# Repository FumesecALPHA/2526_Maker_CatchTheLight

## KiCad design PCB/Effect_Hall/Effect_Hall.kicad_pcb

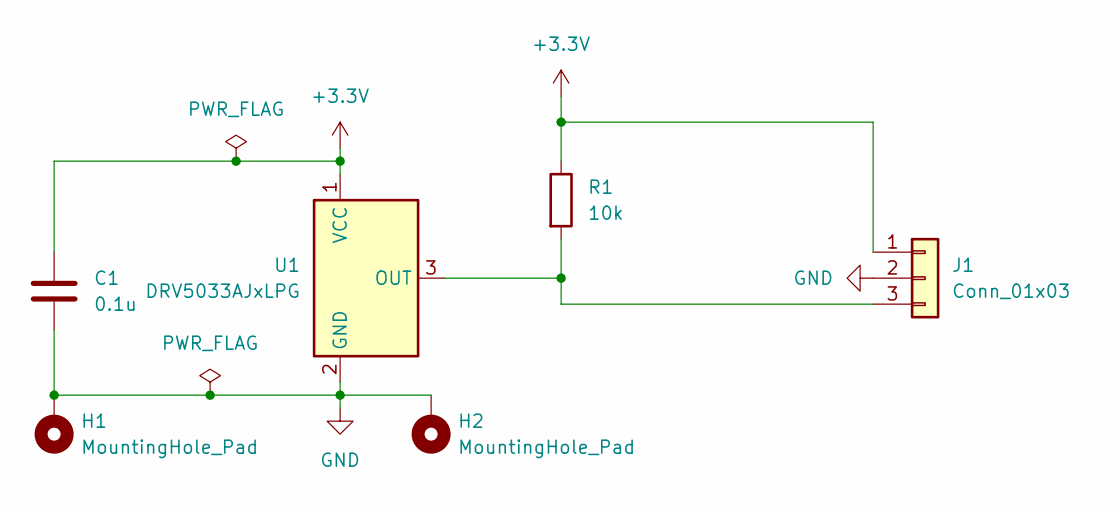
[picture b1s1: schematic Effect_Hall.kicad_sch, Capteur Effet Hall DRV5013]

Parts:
C1: 0.1u; C_0805_2012Metric_Pad1.18x1.45mm_HandSolder
H1, H2: MountingHole_Pad; MountingHole_2.7mm_M2.5_DIN965_Pad
J1: Conn_01x03; JST_EH_B3B-EH-A_1x03_P2.50mm_Vertical
R1: 10k; R_0805_2012Metric_Pad1.20x1.40mm_HandSolder
U1: DRV5033AJxLPG; TO-92Flat

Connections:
+3.3V: C1.1, J1.1, R1.1, U1.1 (VCC)
GND: C1.2, H1.1, H2.1, J1.2, U1.2 (GND)
unnamed: J1.3, R1.2, U1.3 (OUT)

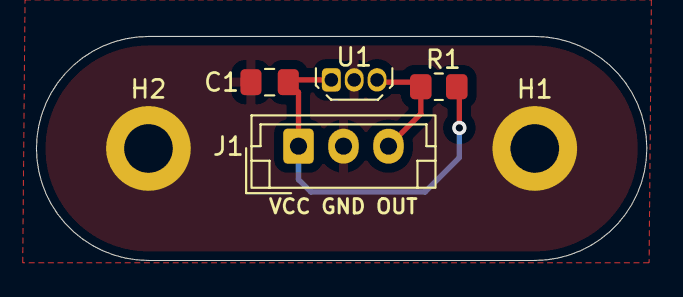
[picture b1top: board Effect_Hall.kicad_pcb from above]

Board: 2 copper layers, 33.9 x 12.4 mm, 6 parts (0 on the bottom side), 3 nets.

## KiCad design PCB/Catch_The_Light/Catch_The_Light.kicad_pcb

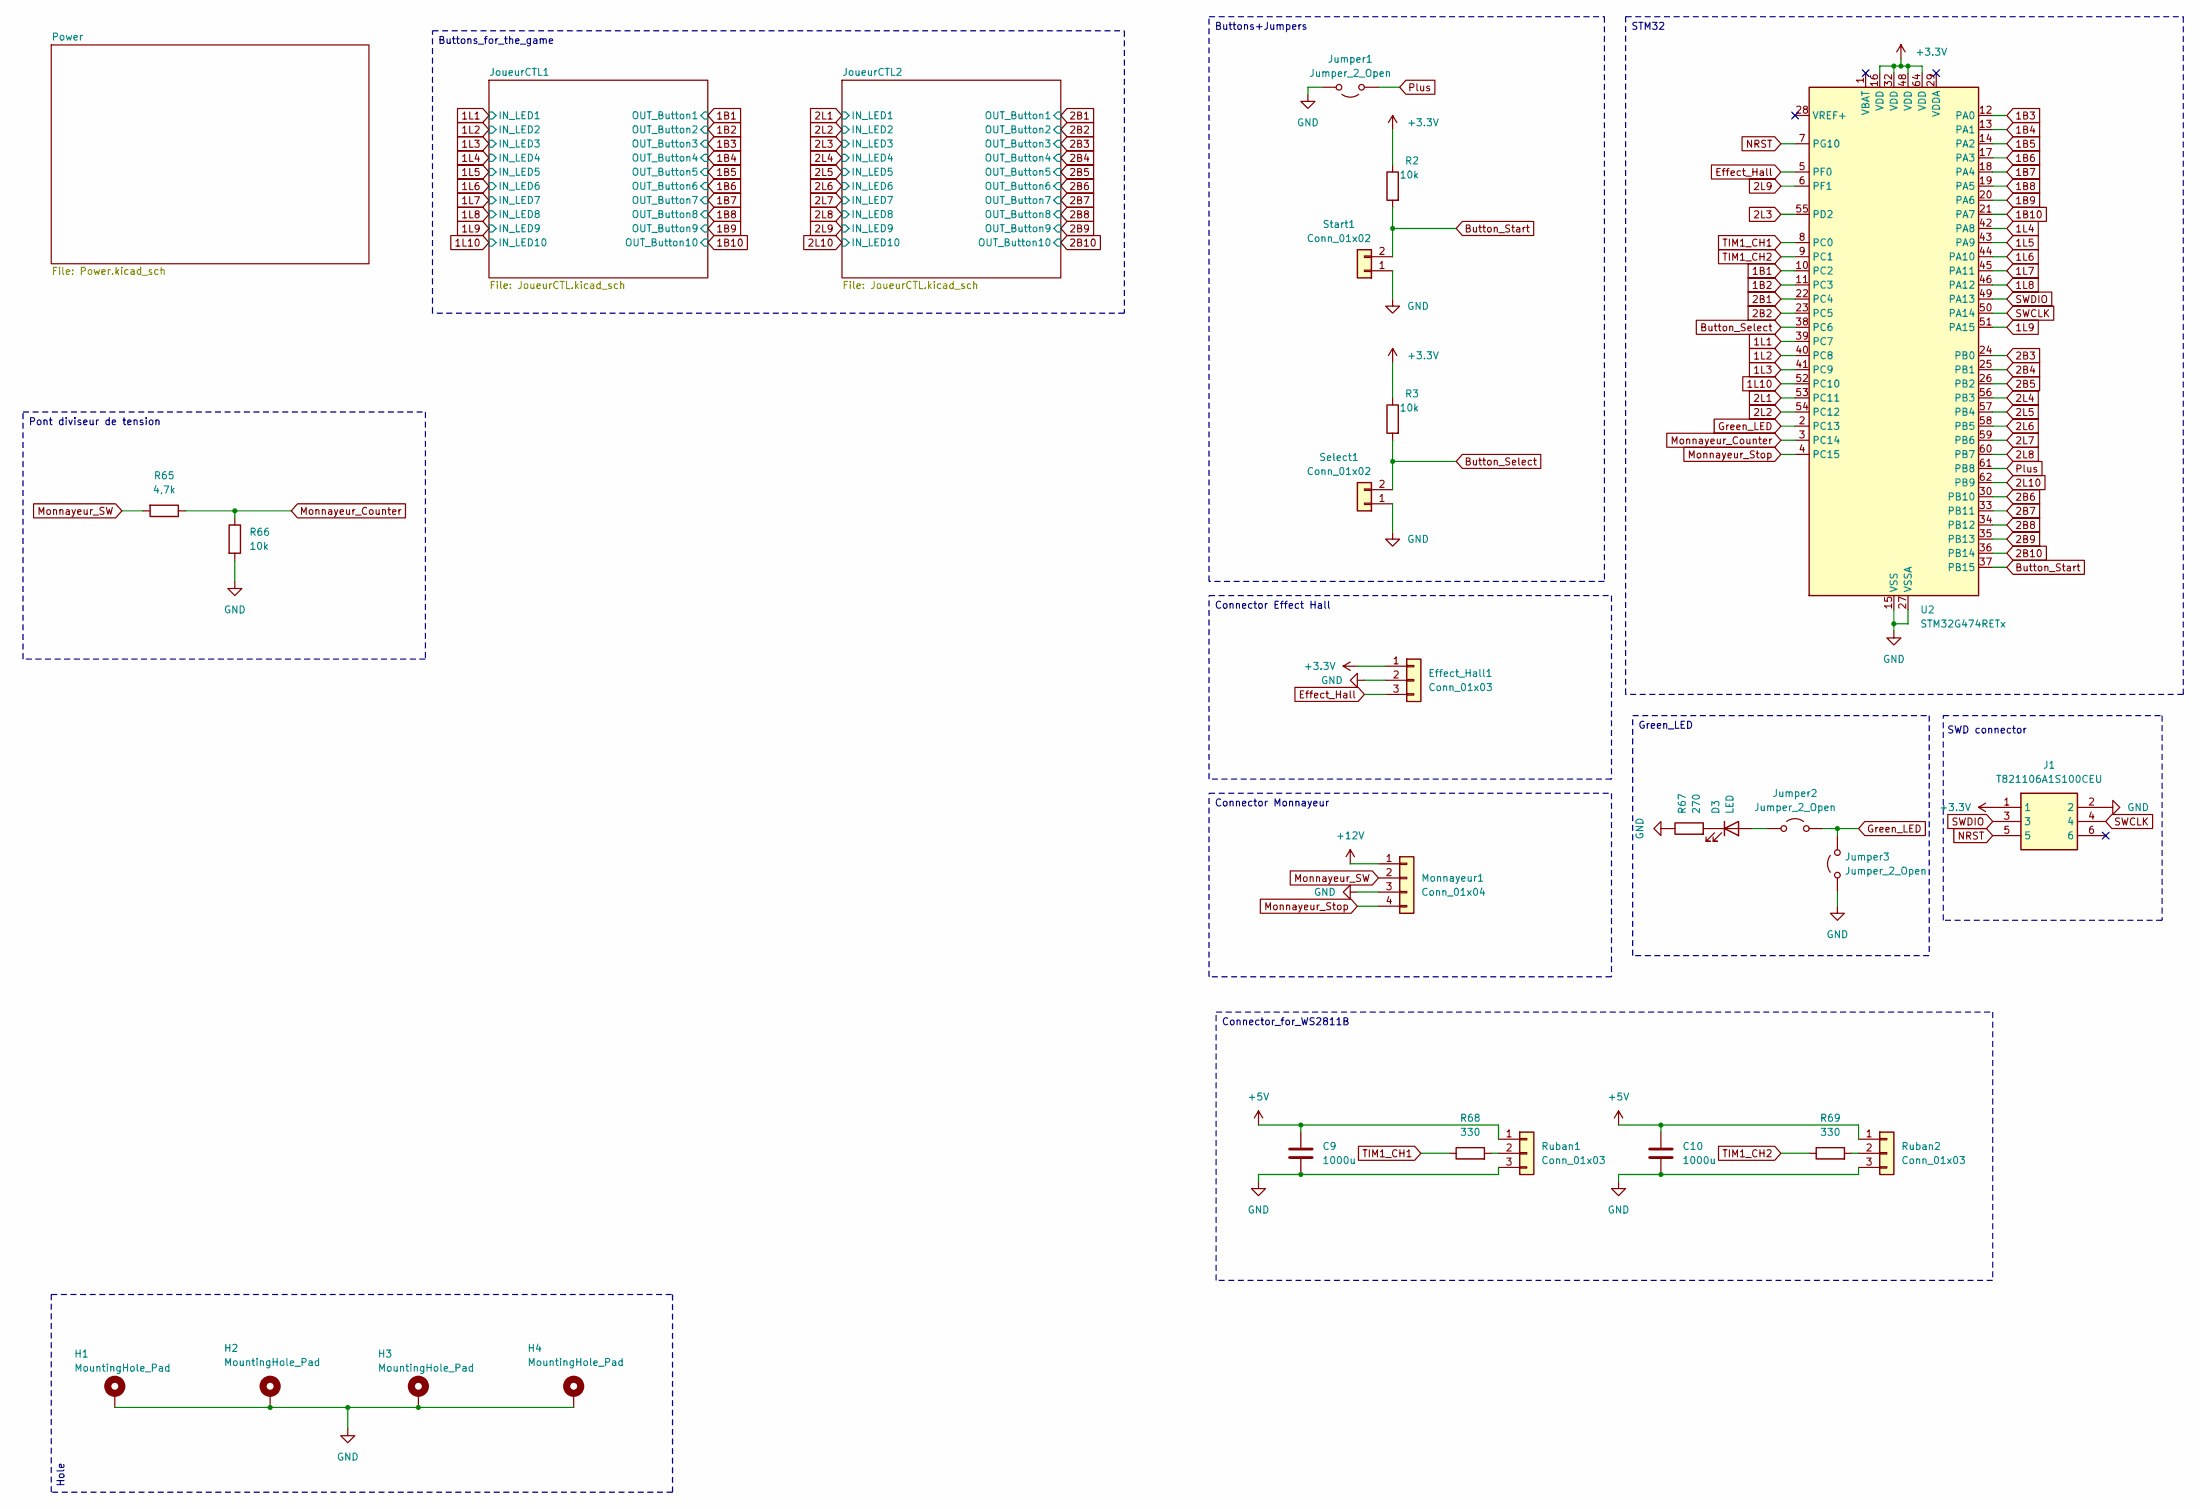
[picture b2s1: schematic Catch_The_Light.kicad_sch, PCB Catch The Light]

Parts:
C9, C10: 1000u; C_0402_1005Metric_Pad0.74x0.62mm_HandSolder
D3: LED; LED_0805_2012Metric_Pad1.15x1.40mm_HandSolder
Effect_Hall1: Conn_01x03; JST_EH_B3B-EH-A_1x03_P2.50mm_Vertical
H1, H2, H3, H4: MountingHole_Pad; MountingHole_3.2mm_M3_DIN965_Pad
J1: T821106A1S100CEU; PinHeader_2x03_P2.54mm_Vertical_SMD; Manufacturer_Part_Number T821106A1S100CEU
Jumper1, Jumper2, Jumper3: Jumper_2_Open; PinHeader_1x02_P2.54mm_Vertical
Monnayeur1: Conn_01x04; JST_EH_B4B-EH-A_1x04_P2.50mm_Vertical
R2, R3, R66: 10k; R_0402_1005Metric_Pad0.72x0.64mm_HandSolder
R65: 4,7k; R_0402_1005Metric_Pad0.72x0.64mm_HandSolder
R67: 270; R_0402_1005Metric_Pad0.72x0.64mm_HandSolder
R68, R69: 330; R_0402_1005Metric_Pad0.72x0.64mm_HandSolder
Ruban1, Ruban2: Conn_01x03; JST_EH_B3B-EH-A_1x03_P2.50mm_Vertical
Select1: Conn_01x02; JST_EH_B2B-EH-A_1x02_P2.50mm_Vertical
Start1: Conn_01x02; JST_EH_B2B-EH-A_1x02_P2.50mm_Vertical
U2: STM32G474RETx; LQFP-64_10x10mm_P0.5mm

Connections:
1B1: U2.10 (PC2); also elsewhere on the board
1B2: U2.11 (PC3); also elsewhere on the board
1B3: U2.12 (PA0); also elsewhere on the board
1B4: U2.13 (PA1); also elsewhere on the board
1B5: U2.14 (PA2); also elsewhere on the board
1B6: U2.17 (PA3); also elsewhere on the board
1B7: U2.18 (PA4); also elsewhere on the board
1B8: U2.19 (PA5); also elsewhere on the board
1B9: U2.20 (PA6); also elsewhere on the board
1B10: U2.21 (PA7); also elsewhere on the board
1L1: U2.39 (PC7); also elsewhere on the board
1L2: U2.40 (PC8); also elsewhere on the board
1L3: U2.41 (PC9); also elsewhere on the board
1L4: U2.42 (PA8); also elsewhere on the board
1L5: U2.43 (PA9); also elsewhere on the board
1L6: U2.44 (PA10); also elsewhere on the board
1L7: U2.45 (PA11); also elsewhere on the board
1L8: U2.46 (PA12); also elsewhere on the board
1L9: U2.51 (PA15); also elsewhere on the board
1L10: U2.52 (PC10); also elsewhere on the board
2B1: U2.22 (PC4); also elsewhere on the board
2B2: U2.23 (PC5); also elsewhere on the board
2B3: U2.24 (PB0); also elsewhere on the board
2B4: U2.25 (PB1); also elsewhere on the board
2B5: U2.26 (PB2); also elsewhere on the board
2B6: U2.30 (PB10); also elsewhere on the board
2B7: U2.33 (PB11); also elsewhere on the board
2B8: U2.34 (PB12); also elsewhere on the board
2B9: U2.35 (PB13); also elsewhere on the board
2B10: U2.36 (PB14); also elsewhere on the board
2L1: U2.53 (PC11); also elsewhere on the board
2L2: U2.54 (PC12); also elsewhere on the board
2L3: U2.55 (PD2); also elsewhere on the board
2L4: U2.56 (PB3); also elsewhere on the board
2L5: U2.57 (PB4); also elsewhere on the board
2L6: U2.58 (PB5); also elsewhere on the board
2L7: U2.59 (PB6); also elsewhere on the board
2L8: U2.60 (PB7); also elsewhere on the board
2L9: U2.6 (PF1); also elsewhere on the board
2L10: U2.62 (PB9); also elsewhere on the board
+3.3V: Effect_Hall1.1, J1.1, R2.1, R3.1, U2.16 (VDD), U2.32 (VDD), U2.48 (VDD), U2.64 (VDD); also elsewhere on the board
+5V: C9.1, C10.1, Ruban1.1, Ruban2.1; also elsewhere on the board
+12V: Monnayeur1.1; also elsewhere on the board
Button_Select: R3.2, Select1.2, U2.38 (PC6)
Button_Start: R2.2, Start1.2, U2.37 (PB15)
Effect_Hall: Effect_Hall1.3, U2.5 (PF0)
GND: C9.2, C10.2, Effect_Hall1.2, H1.1, H2.1, H3.1, H4.1, J1.2, Jumper1.1 (A), Jumper3.2 (B), Monnayeur1.3, R66.2, R67.1, Ruban1.3, Ruban2.3, Select1.1, Start1.1, U2.15 (VSS), U2.27 (VSSA), U2.31 (VSS), U2.47 (VSS), U2.63 (VSS); also elsewhere on the board
Green_LED: Jumper2.1 (A), Jumper3.1 (A), U2.2 (PC13)
Monnayeur_Counter: R65.1, R66.1, U2.3 (PC14)
Monnayeur_SW: Monnayeur1.2, R65.2
Monnayeur_Stop: Monnayeur1.4, U2.4 (PC15)
NRST: J1.5, U2.7 (PG10)
unnamed: D3.2 (A), Jumper2.2 (B)
unnamed: D3.1 (K), R67.2
unnamed: R68.2, Ruban1.2
unnamed: R69.2, Ruban2.2
Plus: Jumper1.2 (B), U2.61 (PB8)
SWCLK: J1.4, U2.50 (PA14)
SWDIO: J1.3, U2.49 (PA13)
TIM1_CH1: R68.1, U2.8 (PC0)
TIM1_CH2: R69.1, U2.9 (PC1)

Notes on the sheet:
SWD connector
Green_LED
Connector Monnayeur
Hole
Buttons_for_the_game
Connector_for_WS2811B
STM32
Pont diviseur de tension
Buttons+Jumpers
Connector Effect Hall

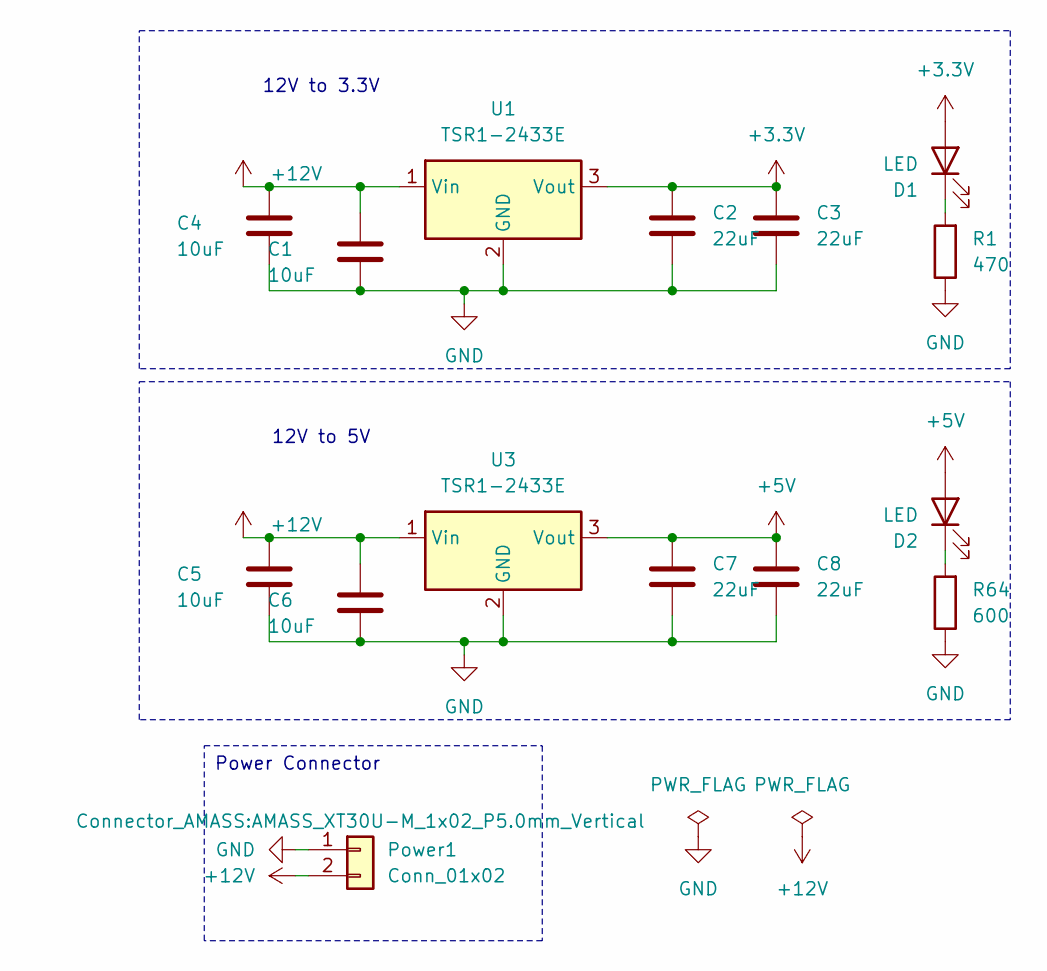
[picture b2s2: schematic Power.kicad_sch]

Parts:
C1, C4, C5, C6: 10uF; C_0402_1005Metric_Pad0.74x0.62mm_HandSolder
C2, C3, C7, C8: 22uF; C_0402_1005Metric_Pad0.74x0.62mm_HandSolder
D1, D2: LED; LED_0805_2012Metric_Pad1.15x1.40mm_HandSolder
Power1: Conn_01x02; AMASS_XT30U-M_1x02_P5.0mm_Vertical
R1: 470; R_0402_1005Metric_Pad0.72x0.64mm_HandSolder
R64: 600; R_0402_1005Metric_Pad0.72x0.64mm_HandSolder
U1, U3: TSR1-2433E; 173010335

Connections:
+3.3V: C2.2, C3.2, D1.2 (A), U1.3 (Vout); also elsewhere on the board
+5V: C7.2, C8.2, D2.2 (A), U3.3 (Vout); also elsewhere on the board
+12V: C1.2, C4.2, C5.2, C6.2, Power1.2, U1.1 (Vin), U3.1 (Vin); also elsewhere on the board
GND: C1.1, C2.1, C3.1, C4.1, C5.1, C6.1, C7.1, C8.1, Power1.1, R1.1, R64.1, U1.2 (GND), U3.2 (GND); also elsewhere on the board
unnamed: D1.1 (K), R1.2
unnamed: D2.1 (K), R64.2

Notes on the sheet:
12V to 5V
12V to 3.3V
Power Connector

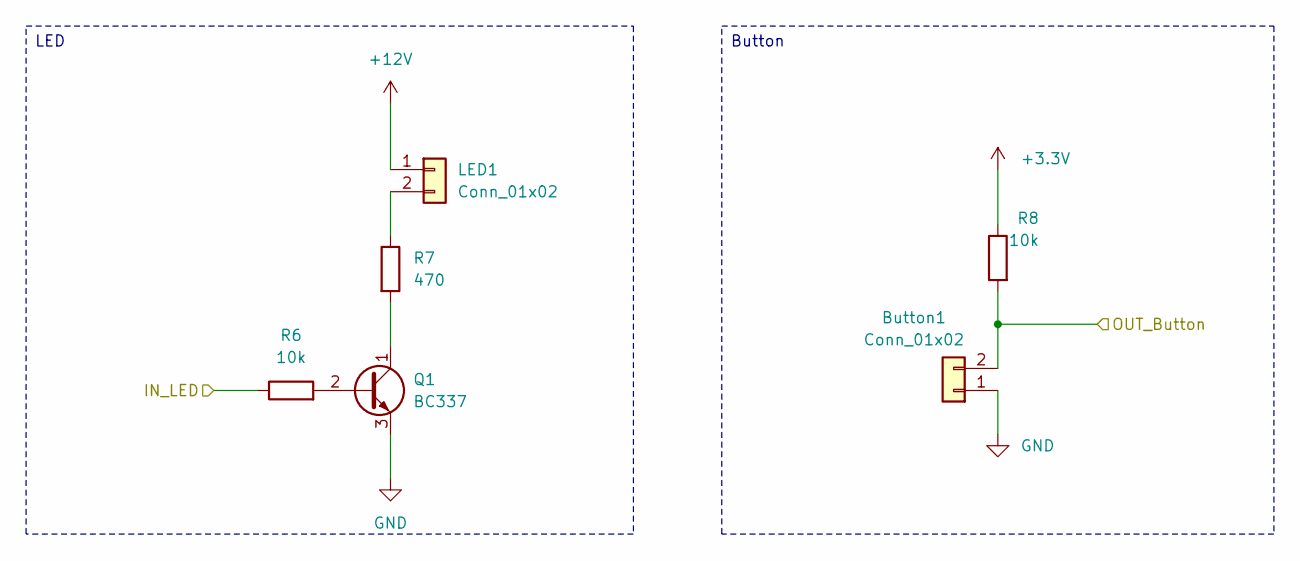
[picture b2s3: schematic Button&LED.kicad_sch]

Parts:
Button1: Conn_01x02; JST_EH_B2B-EH-A_1x02_P2.50mm_Vertical
LED1: Conn_01x02; JST_EH_B2B-EH-A_1x02_P2.50mm_Vertical
Q1: BC337; TO-92_Inline
R6, R8: 10k; R_0402_1005Metric_Pad0.72x0.64mm_HandSolder
R7: 470; R_0402_1005Metric_Pad0.72x0.64mm_HandSolder

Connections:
1B1: Button1.2, R8.2; also elsewhere on the board
1L1: R6.1; also elsewhere on the board
+3.3V: R8.1; also elsewhere on the board
+12V: LED1.1; also elsewhere on the board
GND: Button1.1, Q1.3 (E); also elsewhere on the board
unnamed: LED1.2, R7.1
unnamed: Q1.2 (B), R6.2
unnamed: Q1.1 (C), R7.2

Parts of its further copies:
Button2, Button3, Button4, Button5, Button6, Button7, Button8, Button9, Button10, Button11, Button12, Button13, Button14, Button15, Button16, Button17, Button18, Button19, Button20: Conn_01x02; JST_EH_B2B-EH-A_1x02_P2.50mm_Vertical
LED2, LED3, LED4, LED5, LED6, LED7, LED8, LED9, LED10, LED11, LED12, LED13, LED14, LED15, LED16, LED17, LED18, LED19, LED20: Conn_01x02; JST_EH_B2B-EH-A_1x02_P2.50mm_Vertical
Q2, Q3, Q4, Q5, Q6, Q7, Q8, Q9, Q10, Q11, Q12, Q13, Q14, Q15, Q16, Q17, Q18, Q19, Q20: BC337; TO-92_Inline
R4, R9, R11, R12, R14, R15, R17, R18, R20, R21, R23, R24, R26, R27, R29, R30, R32, R33, R35, R36, R37, R39, R40, R42, R43, R45, R46, R48, R49, R51, R52, R54, R55, R57, R58, R60, R61, R63: 10k; R_0402_1005Metric_Pad0.72x0.64mm_HandSolder
R5, R10, R13, R16, R19, R22, R25, R28, R31, R34, R38, R41, R44, R47, R50, R53, R56, R59, R62: 470; R_0402_1005Metric_Pad0.72x0.64mm_HandSolder

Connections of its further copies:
1B2: Button2.2, R11.2; also elsewhere on the board
1B3: Button3.2, R14.2; also elsewhere on the board
1B4: Button4.2, R17.2; also elsewhere on the board
1B5: Button5.2, R20.2; also elsewhere on the board
1B6: Button6.2, R23.2; also elsewhere on the board
1B7: Button7.2, R26.2; also elsewhere on the board
1B8: Button8.2, R29.2; also elsewhere on the board
1B9: Button9.2, R32.2; also elsewhere on the board
1B10: Button10.2, R35.2; also elsewhere on the board
1L2: R9.1; also elsewhere on the board
1L3: R12.1; also elsewhere on the board
1L4: R15.1; also elsewhere on the board
1L5: R18.1; also elsewhere on the board
1L6: R21.1; also elsewhere on the board
1L7: R24.1; also elsewhere on the board
1L8: R27.1; also elsewhere on the board
1L9: R30.1; also elsewhere on the board
1L10: R33.1; also elsewhere on the board
2B1: Button11.2, R36.2; also elsewhere on the board
2B2: Button12.2, R39.2; also elsewhere on the board
2B3: Button13.2, R42.2; also elsewhere on the board
2B4: Button14.2, R45.2; also elsewhere on the board
2B5: Button15.2, R48.2; also elsewhere on the board
2B6: Button16.2, R51.2; also elsewhere on the board
2B7: Button17.2, R54.2; also elsewhere on the board
2B8: Button18.2, R57.2; also elsewhere on the board
2B9: Button19.2, R60.2; also elsewhere on the board
2B10: Button20.2, R63.2; also elsewhere on the board
2L1: R4.1; also elsewhere on the board
2L2: R37.1; also elsewhere on the board
2L3: R40.1; also elsewhere on the board
2L4: R43.1; also elsewhere on the board
2L5: R46.1; also elsewhere on the board
2L6: R49.1; also elsewhere on the board
2L7: R52.1; also elsewhere on the board
2L8: R55.1; also elsewhere on the board
2L9: R58.1; also elsewhere on the board
2L10: R61.1; also elsewhere on the board
+3.3V: R11.1, R14.1, R17.1, R20.1, R23.1, R26.1, R29.1, R32.1, R35.1, R36.1, R39.1, R42.1, R45.1, R48.1, R51.1, R54.1, R57.1, R60.1, R63.1; also elsewhere on the board
+12V: LED2.1, LED3.1, LED4.1, LED5.1, LED6.1, LED7.1, LED8.1, LED9.1, LED10.1, LED11.1, LED12.1, LED13.1, LED14.1, LED15.1, LED16.1, LED17.1, LED18.1, LED19.1, LED20.1; also elsewhere on the board
GND: Button2.1, Button3.1, Button4.1, Button5.1, Button6.1, Button7.1, Button8.1, Button9.1, Button10.1, Button11.1, Button12.1, Button13.1, Button14.1, Button15.1, Button16.1, Button17.1, Button18.1, Button19.1, Button20.1, Q2.3 (E), Q3.3 (E), Q4.3 (E), Q5.3 (E), Q6.3 (E), Q7.3 (E), Q8.3 (E), Q9.3 (E), Q10.3 (E), Q11.3 (E), Q12.3 (E), Q13.3 (E), Q14.3 (E), Q15.3 (E), Q16.3 (E), Q17.3 (E), Q18.3 (E), Q19.3 (E), Q20.3 (E); also elsewhere on the board
unnamed: LED2.2, R10.1
unnamed: LED3.2, R13.1
unnamed: LED4.2, R16.1
unnamed: LED5.2, R19.1
unnamed: LED6.2, R22.1
unnamed: LED7.2, R25.1
unnamed: LED8.2, R28.1
unnamed: LED9.2, R31.1
unnamed: LED10.2, R34.1
unnamed: LED11.2, R5.1
unnamed: LED12.2, R38.1
unnamed: LED13.2, R41.1
unnamed: LED14.2, R44.1
unnamed: LED15.2, R47.1
unnamed: LED16.2, R50.1
unnamed: LED17.2, R53.1
unnamed: LED18.2, R56.1
unnamed: LED19.2, R59.1
unnamed: LED20.2, R62.1
unnamed: Q2.2 (B), R9.2
unnamed: Q2.1 (C), R10.2
unnamed: Q3.2 (B), R12.2
unnamed: Q3.1 (C), R13.2
unnamed: Q4.2 (B), R15.2
unnamed: Q4.1 (C), R16.2
unnamed: Q5.2 (B), R18.2
unnamed: Q5.1 (C), R19.2
unnamed: Q6.2 (B), R21.2
unnamed: Q6.1 (C), R22.2
unnamed: Q7.2 (B), R24.2
unnamed: Q7.1 (C), R25.2
unnamed: Q8.2 (B), R27.2
unnamed: Q8.1 (C), R28.2
unnamed: Q9.2 (B), R30.2
unnamed: Q9.1 (C), R31.2
unnamed: Q10.2 (B), R33.2
unnamed: Q10.1 (C), R34.2
unnamed: Q11.2 (B), R4.2
unnamed: Q11.1 (C), R5.2
unnamed: Q12.2 (B), R37.2
unnamed: Q12.1 (C), R38.2
unnamed: Q13.2 (B), R40.2
unnamed: Q13.1 (C), R41.2
unnamed: Q14.2 (B), R43.2
unnamed: Q14.1 (C), R44.2
unnamed: Q15.2 (B), R46.2
unnamed: Q15.1 (C), R47.2
unnamed: Q16.2 (B), R49.2
unnamed: Q16.1 (C), R50.2
unnamed: Q17.2 (B), R52.2
unnamed: Q17.1 (C), R53.2
unnamed: Q18.2 (B), R55.2
unnamed: Q18.1 (C), R56.2
unnamed: Q19.2 (B), R58.2
unnamed: Q19.1 (C), R59.2
unnamed: Q20.2 (B), R61.2
unnamed: Q20.1 (C), R62.2

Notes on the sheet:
LED
Button

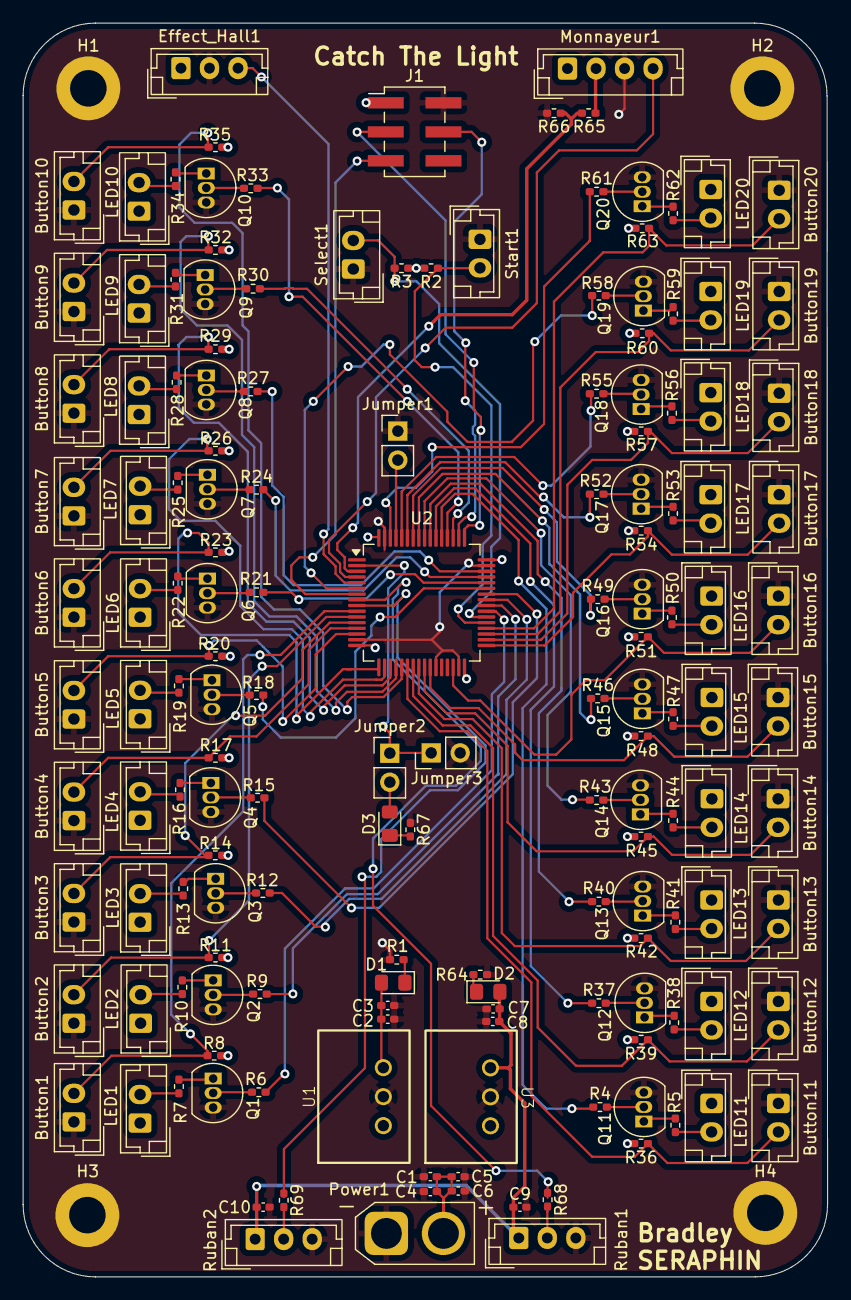
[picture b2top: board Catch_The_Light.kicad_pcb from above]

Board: 4 copper layers, 70.5 x 109.9 mm, 160 parts (0 on the bottom side), 123 nets.

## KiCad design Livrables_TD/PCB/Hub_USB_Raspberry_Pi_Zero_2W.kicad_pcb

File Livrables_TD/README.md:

# Phase 1
## Séance 19 janvier 2026
Durant la séance, les bases des CAD et CAO (Conception Assisté par Ordinateur) ont été abordés.  
Pour la réalisation de modélisation 3D, on utilisera le site __Onshape__.  
L'ensemble des pièces à modéliser sont disponibles sur Onshape avec les liens ci-dessous : 

Exercice|Dimension|Modèle 3D|Lien Onshape
--------|---------|---------|------------
1|||[Exercice 1](https://cad.onshape.com/documents/df037e857c65d72a9e0dcdee/w/5bb3aaa7c1116d4dddbc7c86/e/42c94ab56460c4359e813fc6)
2|||[Exercice 2](https://cad.onshape.com/documents/ca30c9cf2d4c386ce32318bf/w/4f4a85186b39939a6845c0c7/e/ec8557db5ca79b660bbd65a4)
3|||[Exercice 3](https://cad.onshape.com/documents/50b0ced427976d228f21d34d/w/341f5911bb30ec65a4887743/e/47a07ce9751d44de008f68fb)
4|||[Exercice 4](https://cad.onshape.com/documents/157af253f111f99f6e488c92/w/61d451010b018822de329eea/e/95c9f9d9157564ad2d69be4f)
5|||[Exercice 5](https://cad.onshape.com/documents/626da6e0d63fc7d485a7c6f0/w/63b2924a8fe31294c8c51b87/e/ca38073f5bea51096f05ebc5)

## Séance 22 janvier 2026
Une fois la modélisation 3D est réalisé avec Onshape, on passe à l'impression 3D.  
Explication du fonctionnement d'une imprimante 3D, présentation des différents matériaux d'impression et explication des slicers.   
Voici les différentes étapes de l'impression :  

Choix du modèle 3D|Paramètrage du slicer|Impression|Résultat
------------------|---------------------|----------|--------
|||

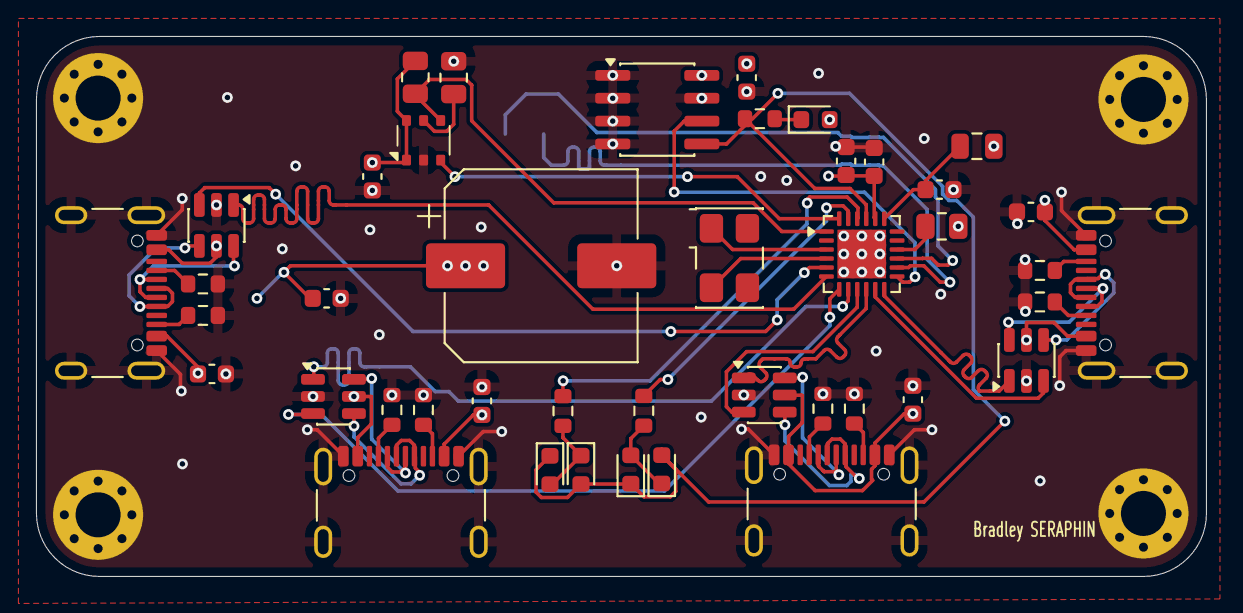
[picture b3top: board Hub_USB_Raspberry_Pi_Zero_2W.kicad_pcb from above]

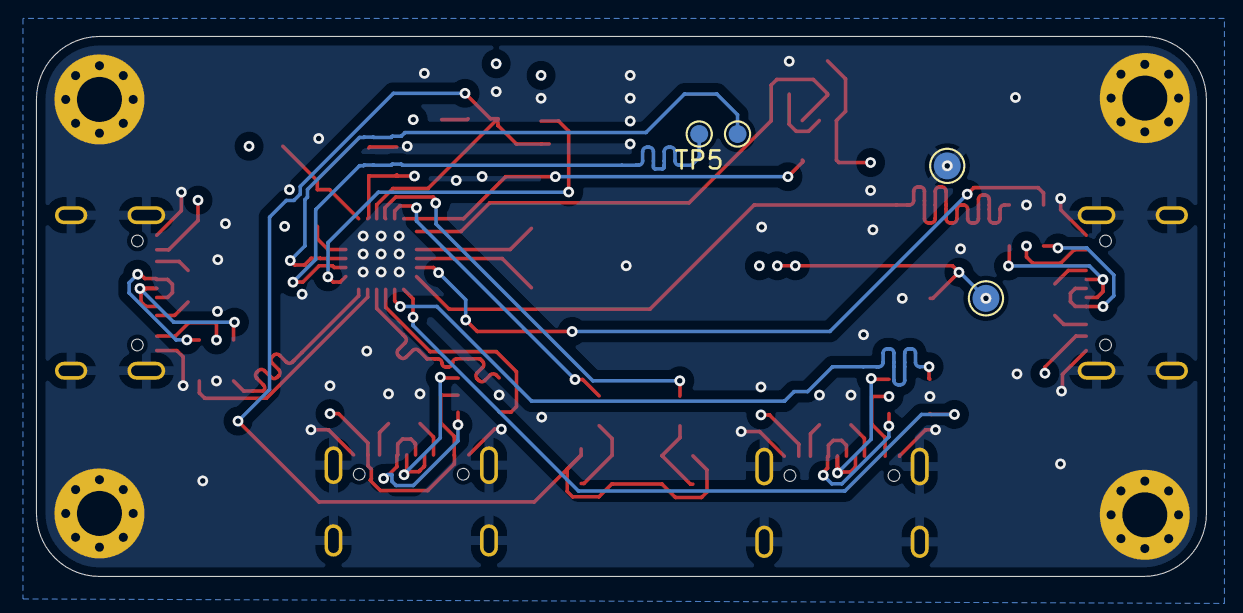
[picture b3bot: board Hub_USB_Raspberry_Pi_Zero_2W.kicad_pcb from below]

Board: 4 copper layers, 65.0 x 30.0 mm, 51 parts (4 on the bottom side), 43 nets.

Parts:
C1, C3, C9: 10uF; C_0603_1608Metric
C2: 0.1uF; C_0603_1608Metric
C4: 100nF; C_0603_1608Metric
C5, C6, C7, C8: 100uF; C_0603_1608Metric
C11: 1uF; C_0603_1608Metric
C101: 470uF; CP_Elec_10x10.5
CH217K1: CH217K; CH217DS1
D1, D2, D3, D4: GREEN_LED; LED_0603_1608Metric
D5: RED_LED; LED_0603_1608Metric
H101, H102, H103, H104: MountingHole_Pad; MountingHole_2.5mm_Pad_Via
J1, J2, J3, J4: USB_C_Receptacle_USB2.0_16P; USB_C_Receptacle_GCT_USB4105-xx-A_16P_TopMnt_Horizontal
R1: 0; Fuse_0805_2012Metric
R2, R5: 220; R_0603_1608Metric
R3, R4, R10, R11, R100, R110, R300, R400: 5.1k; R_0603_1608Metric
R6: 10k; R_0603_1608Metric
R7: NC(56k); R_0805_2012Metric
R8: 56k; R_0805_2012Metric
R9: NC(4k7); R_0805_2012Metric
TP5: Data -; TestPoint_Pad_D1.0mm
TP6: Data +; TestPoint_Pad_D1.0mm
TP7: Alim; TestPoint_Pad_D1.5mm
TP8: Masse; TestPoint_Pad_D1.5mm
U1, U2, U3, U4: USBLC6-2SC6; SOT-23-6
U5: 24C02Cx-x-SN; SOIC-8_3.9x4.9mm_P1.27mm
U6: CH334F; QFN-24-1EP_4x4mm_P0.5mm_EP2.7x2.7mm
Y1: 12 MHZ; Crystal_SMD_5032-4Pin_5.0x3.2mm

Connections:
+3V3: C1.1, C2.1, C4.1, D5.2 (A), R9.1, U5.8 (VCC), U6.20 (VDD33_{LDO})
+5V: C5.1, C6.1, C7.1, C8.1, C9.1, C11.1, C101.1, CH217K1.1 (VIN), CH217K1.6 (VOUT), J1.A4 (VBUS), J1.A9 (VBUS), J1.B4 (VBUS), J1.B9 (VBUS), J2.A4 (VBUS), J2.A9 (VBUS), J2.B4 (VBUS), J2.B9 (VBUS), J3.A4 (VBUS), J3.A9 (VBUS), J3.B4 (VBUS), J3.B9 (VBUS), J4.A4 (VBUS), J4.A9 (VBUS), J4.B4 (VBUS), J4.B9 (VBUS), R1.1, R7.2, TP7.1, U1.5 (VBUS), U2.5 (VBUS), U3.5 (VBUS), U4.5 (VBUS)
/USB1/D+: J2.A6 (D+), J2.B6 (D+), U2.4 (I/O2)
/USB1/D-: J2.A7 (D-), J2.B7 (D-), U2.6 (I/O1)
/USB2/D+: J3.A6 (D+), J3.B6 (D+), U3.4 (I/O2)
/USB2/D-: J3.A7 (D-), J3.B7 (D-), U3.6 (I/O1)
/USB3/D+: J4.A6 (D+), J4.B6 (D+), U4.4 (I/O2)
/USB3/D-: J4.A7 (D-), J4.B7 (D-), U4.6 (I/O1)
/USB HUB controller/DM1-: U1.3 (I/O2), U6.11 (DM1-)
/USB HUB controller/DM2-: U2.3 (I/O2), U6.9 (DM2-)
/USB HUB controller/DM3-: U3.3 (I/O2), U6.7 (DM3-)
/USB HUB controller/DM4-: U4.3 (I/O2), U6.5 (DM4-)
/USB HUB controller/DP1+: U1.1 (I/O1), U6.12 (DP1+)
/USB HUB controller/DP2+: U2.1 (I/O1), U6.10 (DP2+)
/USB HUB controller/DP3+: U3.1 (I/O1), U6.8 (DP3+)
/USB HUB controller/DP4+: U4.1 (I/O1), U6.6 (DP4+)
/USB HUB controller/LED1: R2.1, U6.22 (LED1)
/USB HUB controller/LED2: R5.1, U6.23 (LED2)
/USB HUB controller/LED3/SCL: U5.6 (SCL), U6.13 (LED3/SCL)
/USB HUB controller/LED4/SDA: D1.2 (A), D2.1 (K), D3.1 (K), D4.2 (A), R6.1, U5.5 (SDA), U6.21 (LED4/SDA)
/USB HUB controller/OVCUR#: CH217K1.4 (FLAG#), R7.1, U6.1 (~OVCUR)
/USB HUB controller/~PWREN: CH217K1.3 (EN#), U6.24 (~PWREN)
/USB/D+: J1.A6 (D+), J1.B6 (D+), U1.4 (I/O2)
/USB/D-: J1.A7 (D-), J1.B7 (D-), U1.6 (I/O1)
GND: C1.2, C2.2, C3.2, C4.2, C5.2, C6.2, C7.2, C8.2, C9.2, C11.2, C101.2, CH217K1.2 (GND), H101.1, H102.1, H103.1, H104.1, J1.A1 (GND), J1.A12 (GND), J1.B1 (GND), J1.B12 (GND), J1.S1 (SHIELD), J2.A1 (GND), J2.A12 (GND), J2.B1 (GND), J2.B12 (GND), J2.S1 (SHIELD), J3.A1 (GND), J3.A12 (GND), J3.B1 (GND), J3.B12 (GND), J3.S1 (SHIELD), J4.A1 (GND), J4.A12 (GND), J4.B1 (GND), J4.B12 (GND), J4.S1 (SHIELD), R3.2, R4.2, R8.1, R10.2, R11.2, R100.2, R110.2, R300.2, R400.2, TP8.1, U1.2 (GND), U2.2 (GND), U3.2 (GND), U4.2 (GND), U5.1 (A0), U5.2 (A1), U5.3 (A2), U5.4 (GND), U5.7 (WP), U6.25 (GND)
unnamed: CH217K1.5 (ISET), R8.2
unnamed: D1.1 (K), D2.2 (A), R2.2
unnamed: D3.2 (A), D4.1 (K), R5.2
unnamed: D5.1 (K), R6.2
unnamed: J1.A5 (CC1), R100.1
unnamed: J1.B5 (CC2), R110.1
unnamed: J2.A5 (CC1), R300.1
unnamed: J2.B5 (CC2), R400.1
unnamed: J3.A5 (CC1), R3.1
unnamed: J3.B5 (CC2), R4.1
unnamed: J4.A5 (CC1), R10.1
unnamed: J4.B5 (CC2), R11.1
unnamed: TP5.1, U6.14 (DMU-)
unnamed: TP6.1, U6.15 (DPU+)
unnamed: C3.1, R1.2, U6.19 (V5)
unnamed: U6.4 (XI), Y1.2
unnamed: U6.3 (XO), Y1.1
unnamed: R9.2, U6.16 (~RESET/CDP)

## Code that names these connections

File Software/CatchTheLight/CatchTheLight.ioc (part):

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Mcu.Name=STM32G474R(B-C-E)Tx
Mcu.Package=LQFP64
Mcu.UserName=STM32G474RETx
PA0.GPIOParameters=GPIO_Label
PA0.GPIO_Label=_1B3
PA0.Signal=GPIO_Input
PA1.GPIOParameters=GPIO_Label
PA1.GPIO_Label=_1B4
PA1.Signal=GPIO_Input
PA10.GPIOParameters=GPIO_Label
PA10.GPIO_Label=_1L6
PA10.Signal=GPIO_Output
PA11.GPIOParameters=GPIO_Label
PA11.GPIO_Label=_1L7
PA11.Signal=GPIO_Output
PA12.GPIOParameters=GPIO_Label
PA12.GPIO_Label=_1L8
PA12.Signal=GPIO_Output
PA13.Mode=Serial_Wire
PA13.Signal=SYS_JTMS-SWDIO
PA14.Mode=Serial_Wire
PA14.Signal=SYS_JTCK-SWCLK
PA15.GPIOParameters=GPIO_Label
PA15.GPIO_Label=_1L9
PA15.Signal=GPIO_Output
PA2.GPIOParameters=GPIO_Label
PA2.GPIO_Label=_1B5
PA2.Signal=GPIO_Input
PA3.GPIOParameters=GPIO_Label
PA3.GPIO_Label=_1B6
PA3.Signal=GPIO_Input
PA4.GPIOParameters=GPIO_Label
PA4.GPIO_Label=_1B7
PA4.Signal=GPIO_Input
PA5.GPIOParameters=GPIO_Label
PA5.GPIO_Label=_1B8
PA5.Signal=GPIO_Input
PA6.GPIOParameters=GPIO_Label
PA6.GPIO_Label=_1B9
PA6.Signal=GPIO_Input
PA7.GPIOParameters=GPIO_Label
PA7.GPIO_Label=_1B10
PA7.Signal=GPIO_Input
PA8.GPIOParameters=GPIO_Label
PA8.GPIO_Label=_1L4
PA8.Signal=GPIO_Output
PA9.GPIOParameters=GPIO_Label
PA9.GPIO_Label=_1L5
PA9.Signal=GPIO_Output
PB0.GPIOParameters=GPIO_Label
PB0.GPIO_Label=_2B3
PB0.Signal=GPIO_Input
PB1.GPIOParameters=GPIO_Label
PB1.GPIO_Label=_2B4
PB1.Signal=GPIO_Input
PB10.GPIOParameters=GPIO_Label
PB10.GPIO_Label=_2B6
PB10.Signal=GPIO_Input
PB11.GPIOParameters=GPIO_Label
PB11.GPIO_Label=_2B7
PB11.Signal=GPIO_Input
PB12.GPIOParameters=GPIO_Label
PB12.GPIO_Label=_2B8
PB12.Signal=GPIO_Input
PB13.GPIOParameters=GPIO_Label
PB13.GPIO_Label=_2B9
PB13.Signal=GPIO_Input
PB14.GPIOParameters=GPIO_Label
PB14.GPIO_Label=_2B10
PB14.Signal=GPIO_Input
PB15.GPIOParameters=GPIO_Label
PB15.GPIO_Label=Button_Start
PB15.Signal=GPIO_Input
PB2.GPIOParameters=GPIO_Label
PB2.GPIO_Label=_2B5
PB2.Signal=GPIO_Input
PB3.GPIOParameters=GPIO_Label
PB3.GPIO_Label=_2L4
PB3.Signal=GPIO_Output
PB4.GPIOParameters=GPIO_Label
PB4.GPIO_Label=_2L5
PB4.Signal=GPIO_Output
PB5.GPIOParameters=GPIO_Label
PB5.GPIO_Label=_2L6
PB5.Signal=GPIO_Output
PB6.GPIOParameters=GPIO_Label
PB6.GPIO_Label=_2L7
PB6.Signal=GPIO_Output
PB7.GPIOParameters=GPIO_Label
PB7.GPIO_Label=_2L8
PB7.Signal=GPIO_Output
PB9.GPIOParameters=GPIO_Label
PB9.GPIO_Label=_2L10
PB9.Signal=GPIO_Output
PC0.Signal=S_TIM1_CH1
PC10.GPIOParameters=GPIO_Label
PC10.GPIO_Label=_1L10
PC10.Signal=GPIO_Output
PC11.GPIOParameters=GPIO_Label
PC11.GPIO_Label=_2L1
PC11.Signal=GPIO_Output
PC12.GPIOParameters=GPIO_Label
PC12.GPIO_Label=_2L2
PC12.Signal=GPIO_Output
PC13.GPIOParameters=GPIO_Label
PC13.GPIO_Label=Green_LED
PC13.Signal=GPIO_Output
PC14-OSC32_IN.GPIOParameters=GPIO_Label
PC14-OSC32_IN.GPIO_Label=Monnayeur_Counter
PC14-OSC32_IN.Signal=GPXTI14
PC15-OSC32_OUT.GPIOParameters=GPIO_Label
PC15-OSC32_OUT.GPIO_Label=Monnayeur_Stop
PC15-OSC32_OUT.Signal=GPIO_Output
PC2.GPIOParameters=GPIO_Label
PC2.GPIO_Label=_1B1
PC2.Signal=GPIO_Input
PC3.GPIOParameters=GPIO_Label
PC3.GPIO_Label=_1B2
PC3.Signal=GPIO_Input
PC4.GPIOParameters=GPIO_Label
PC4.GPIO_Label=_2B1
PC4.Signal=GPIO_Input
PC5.GPIOParameters=GPIO_Label
PC5.GPIO_Label=_2B2
PC5.Signal=GPIO_Input
PC6.GPIOParameters=GPIO_Label
PC6.GPIO_Label=Button_Select
PC6.Signal=GPIO_Input
PC7.GPIOParameters=GPIO_Label
PC7.GPIO_Label=_1L1
PC7.Signal=GPIO_Output
PC8.GPIOParameters=GPIO_Label
PC8.GPIO_Label=_1L2
PC8.Signal=GPIO_Output
PC9.GPIOParameters=GPIO_Label
PC9.GPIO_Label=_1L3
PC9.Signal=GPIO_Output
PD2.GPIOParameters=GPIO_Label
PD2.GPIO_Label=_2L3
PD2.Signal=GPIO_Output
PF0-OSC_IN.GPIOParameters=GPIO_Label
PF0-OSC_IN.GPIO_Label=Effect_Hall
PF0-OSC_IN.Signal=GPIO_Input
PF1-OSC_OUT.GPIOParameters=GPIO_Label
PF1-OSC_OUT.GPIO_Label=_2L9
PF1-OSC_OUT.Signal=GPIO_Output
RCC.HSE_VALUE=8000000
RCC.SYSCLKFreq_VALUE=80000000
RCC.SYSCLKSource=RCC_SYSCLKSOURCE_PLLCLK
board=custom

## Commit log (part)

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2026-05-03 Impression3D
2026-05-03 media
2026-05-05 Rename Livrables.md to README.md
2026-05-05 Code
2026-05-05 Add project video link to Lien_Video_Projet.md
